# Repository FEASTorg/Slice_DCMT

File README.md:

# DC Motor Driver IC Carrier

DC Motor Driver IC Carrier Slice for BREAD.

## Introduction

[Short introduction on the project.]

## Usage

[Explain how to use the project. Include examples and screenshots if applicable.]

## Documentation

Please refer to the [docs](/docs) for more info.

---

<div align="center">
  
</div>

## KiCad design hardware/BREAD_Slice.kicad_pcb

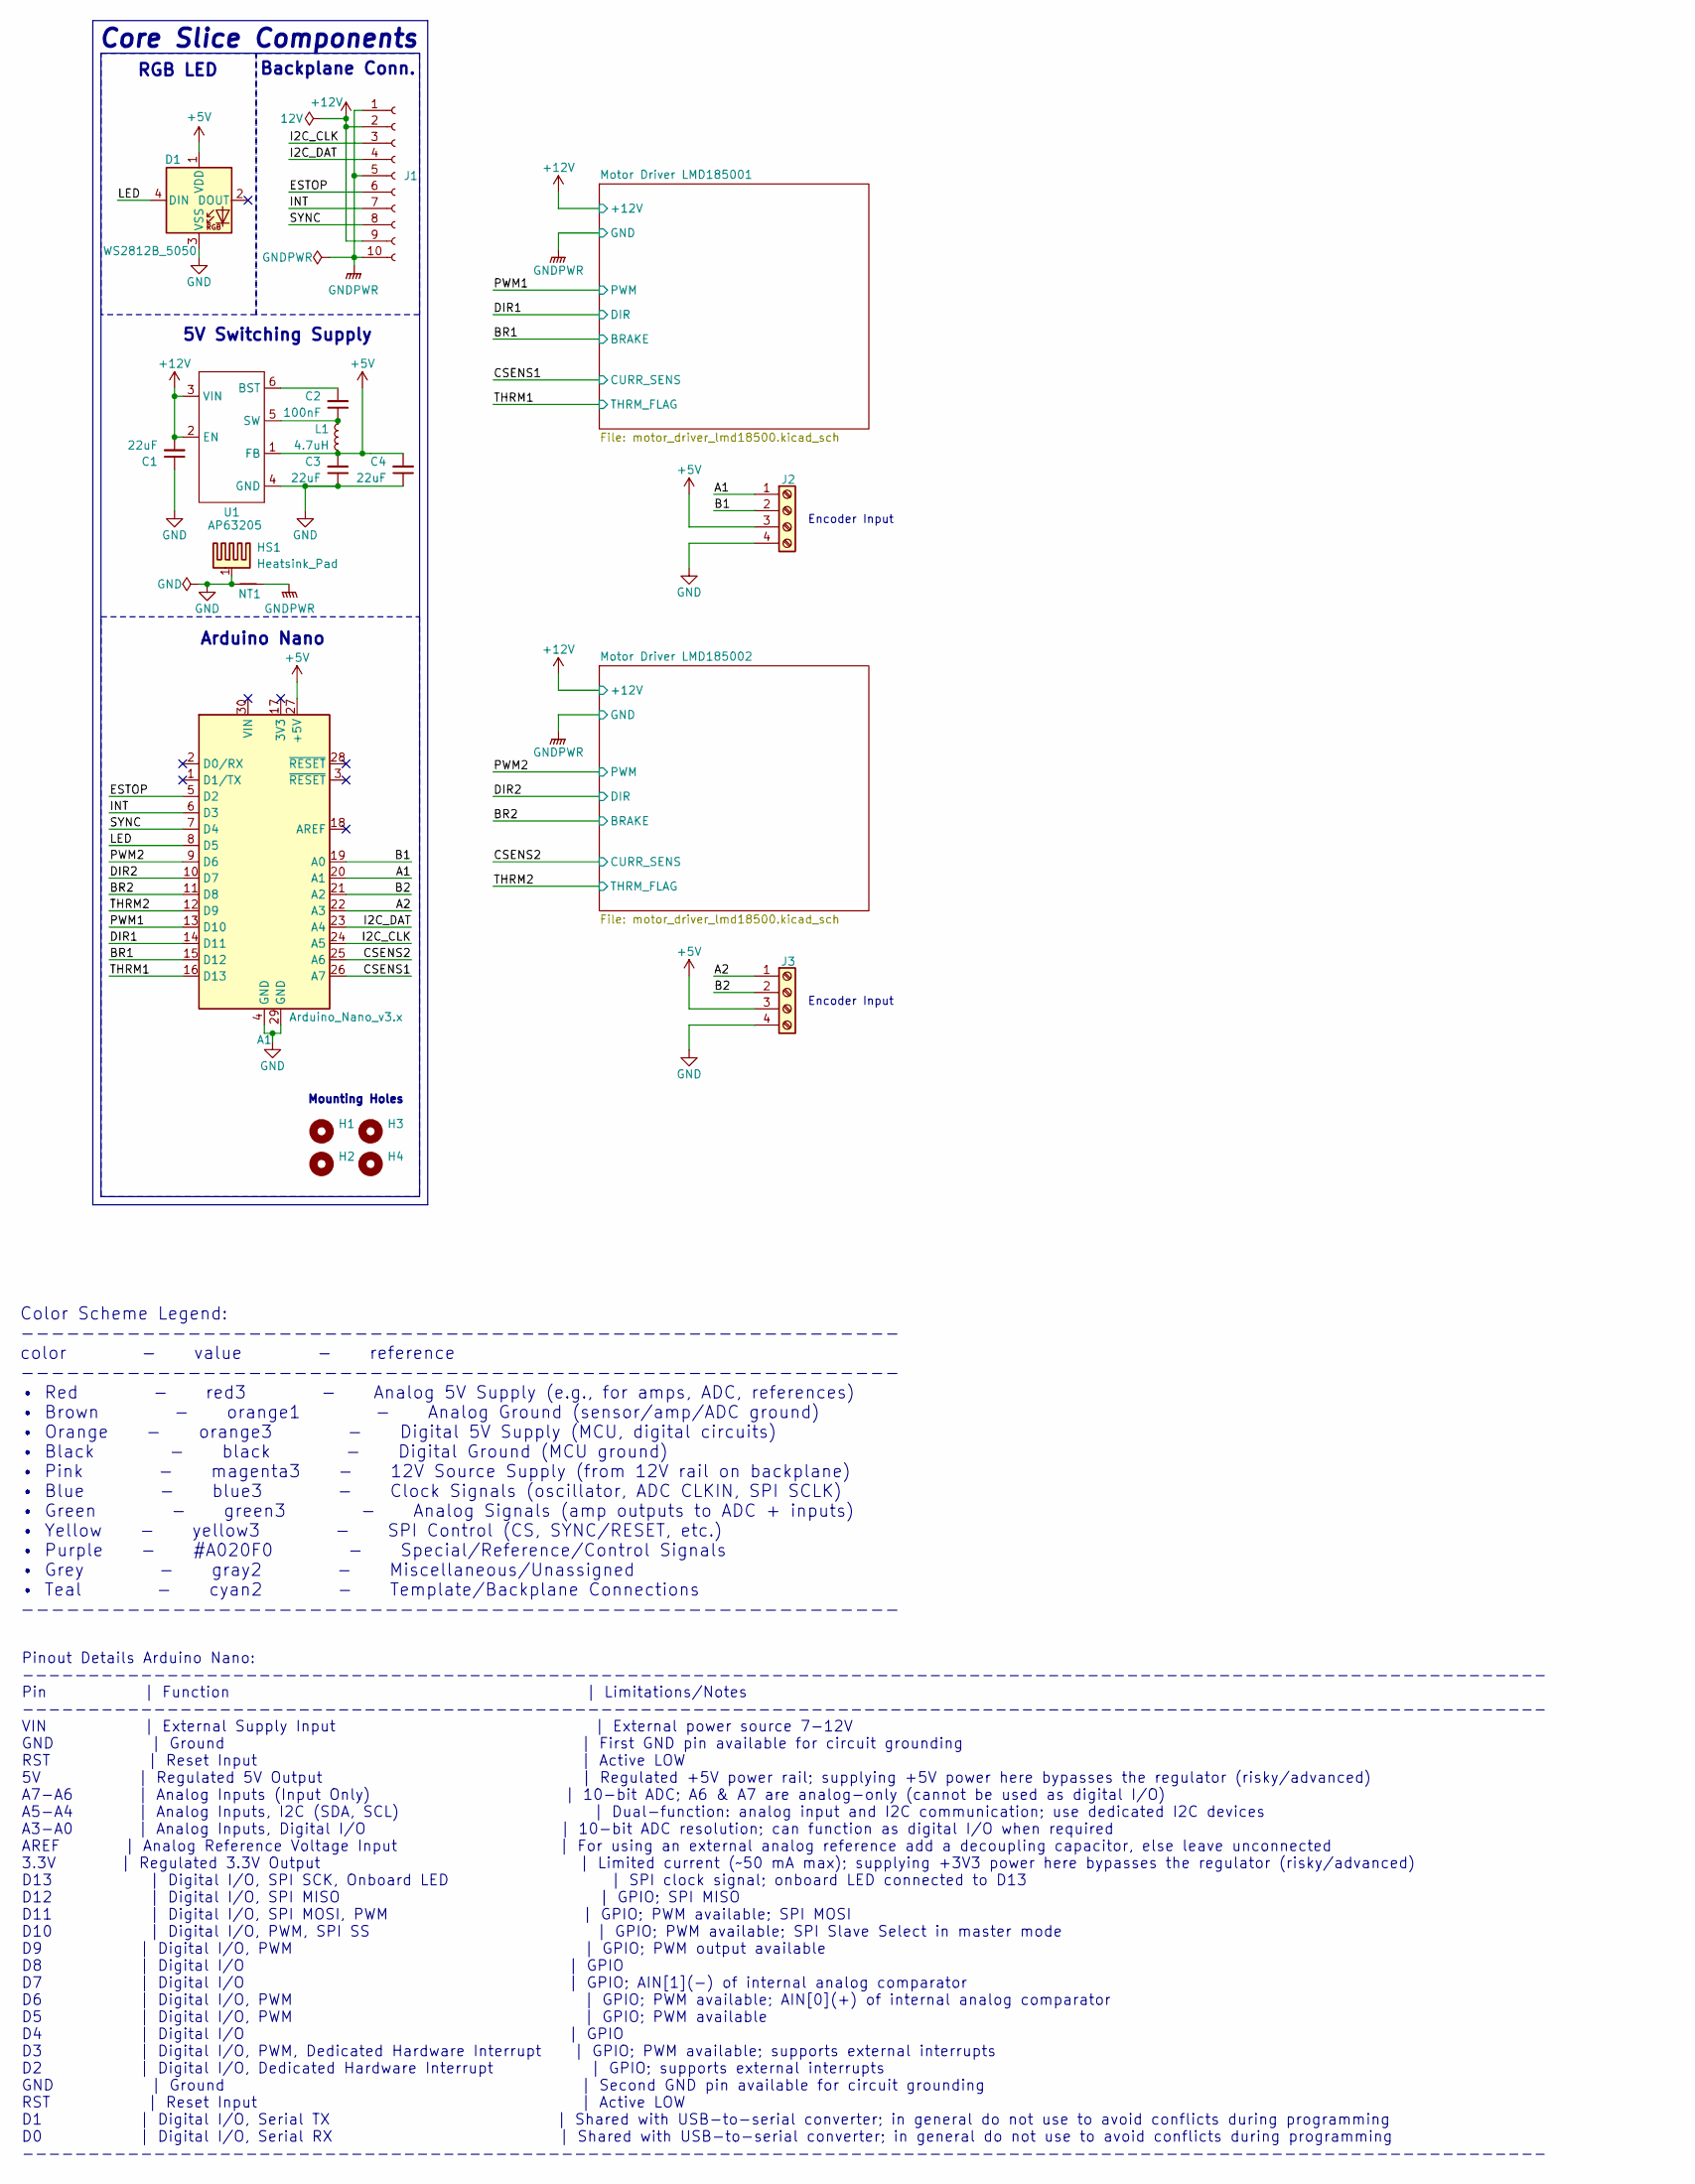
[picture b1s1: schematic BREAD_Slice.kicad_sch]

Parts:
A1: Arduino_Nano_v3.x; Arduino_Nano
C1, C3, C4: 22uF; C_1206_3216Metric
C2: 100nF; C_1206_3216Metric
D1: WS2812B_5050; WS2812-5050-4PIN
H1, H2, H3, H4: MountingHole; MountingHole_5mm
HS1: Heatsink_Pad; Thermal_Pad
J1: Conn_01x10_Socket; PinSocket_1x10_P2.54mm_Horizontal
J2, J3: Screw_Terminal_01x04; TerminalBlock_TE_282834-4_1x04_P2.54mm_Horizontal
L1: 4.7uH; L_1210_3225Metric
NT1: NetTie_2; NetTie-2_SMD_Pad2.0mm
U1: AP63205; SOIC_05WU-7_DIO

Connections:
+5V: A1.27 (+5V), C3.2, C4.2, D1.1 (VDD), J2.3, J3.3, L1.2, U1.1 (FB)
+12V: C1.2, J1.2, J1.9, U1.2 (EN), U1.3 (VIN); also elsewhere on the board
/A1: A1.20 (A1), J2.1
/A2: A1.22 (A3), J3.1
/B1: A1.19 (A0), J2.2
/B2: A1.21 (A2), J3.2
/BR1: A1.15 (D12); also elsewhere on the board
/BR2: A1.11 (D8); also elsewhere on the board
/CSENS1: A1.26 (A7); also elsewhere on the board
/CSENS2: A1.25 (A6); also elsewhere on the board
/DIR1: A1.14 (D11); also elsewhere on the board
/DIR2: A1.10 (D7); also elsewhere on the board
/ESTOP: A1.5 (D2), J1.6
/I2C_CLK: A1.24 (A5), J1.3
/I2C_DAT: A1.23 (A4), J1.4
/INT: A1.6 (D3), J1.7
/LED: A1.8 (D5), D1.4 (DIN)
/PWM1: A1.13 (D10); also elsewhere on the board
/PWM2: A1.9 (D6); also elsewhere on the board
/SYNC: A1.7 (D4), J1.8
/THRM1: A1.16 (D13); also elsewhere on the board
/THRM2: A1.12 (D9); also elsewhere on the board
GND: A1.4 (GND), A1.29 (GND), C1.1, C3.1, C4.1, D1.3 (VSS), HS1.1, J2.4, J3.4, NT1.1, U1.4 (GND)
GNDPWR: J1.1, J1.5, J1.10, NT1.2; also elsewhere on the board
unnamed: C2.2, U1.6 (BST)
unnamed: C2.1, L1.1, U1.5 (SW)

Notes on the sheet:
5V Switching Supply
Pinout Details Arduino Nano: -------------------------------------------------------------------------------------------------------------------- Pin | Function | Limitations/Notes -------------------------------------------------------------------------------------------------------------------- V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
RGB LED
Encoder Input
Color Scheme Legend: ---------------------------------------------------------- color - value - reference ---------------------------------------------------------- • Red - red3 - Analog 5V Supply (e.g., for amps, ADC, references) • Brown - orange1 - Analog Ground (sensor/amp/ADC ground) • Orange -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
Core Slice Components
Arduino Nano
Mounting Holes
Backplane Conn.

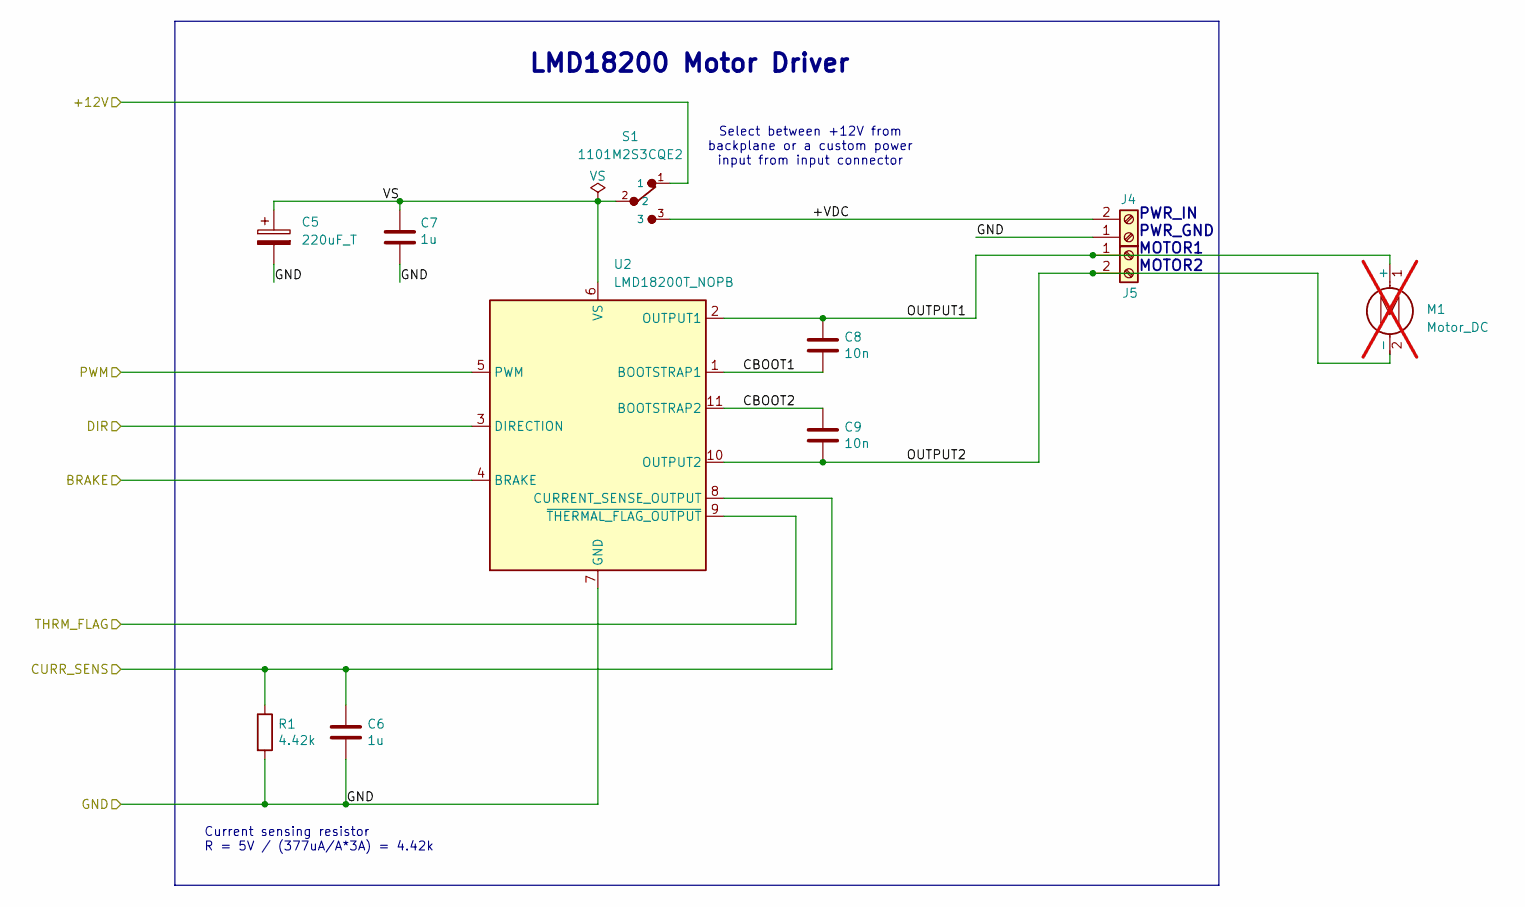
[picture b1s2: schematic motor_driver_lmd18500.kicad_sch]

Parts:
C5: 220uF_T; CP_Radial_D10.0mm_P5.00mm
C6, C7: 1u; C_1206_3216Metric_Pad1.33x1.80mm_HandSolder
C8, C9: 10n; C_0603_1608Metric_Pad1.08x0.95mm_HandSolder
J4, J5: Screw_Terminal_01x02; TerminalBlock_4Ucon_1x02_P3.50mm_Horizontal
M1: Motor_DC; not fitted
R1: 4.42k; R_1206_3216Metric_Pad1.30x1.75mm_HandSolder
S1: 1101M2S3CQE2; SW_Slide-CK-1101M2S3CQE2
U2: LMD18200T_NOPB; TO-220-11_P3.4x5.08mm_StaggerOdd_Lead8.45mm_TabDown

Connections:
+12V: S1.1; also elsewhere on the board
/BR1: U2.4 (BRAKE); also elsewhere on the board
/CSENS1: C6.1, R1.1, U2.8 (CURRENT_SENSE_OUTPUT); also elsewhere on the board
/DIR1: U2.3 (DIRECTION); also elsewhere on the board
/Motor Driver LMD185001/+VDC: J4.2, S1.3
/Motor Driver LMD185001/CBOOT1: C8.2, U2.1 (BOOTSTRAP1)
/Motor Driver LMD185001/CBOOT2: C9.1, U2.11 (BOOTSTRAP2)
/Motor Driver LMD185001/OUTPUT1: C8.1, J5.1, U2.2 (OUTPUT1)
/Motor Driver LMD185001/OUTPUT2: C9.2, J5.2, U2.10 (OUTPUT2)
/Motor Driver LMD185001/VS: C5.1, C7.1, S1.2, U2.6 (VS)
/PWM1: U2.5 (PWM); also elsewhere on the board
/THRM1: U2.9 (~THERMAL_FLAG_OUTPUT); also elsewhere on the board
GNDPWR: C5.2, C6.2, C7.2, J4.1, R1.2, U2.7 (GND); also elsewhere on the board

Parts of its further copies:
C10: 220uF_T; CP_Radial_D10.0mm_P5.00mm
C11, C12: 1u; C_1206_3216Metric_Pad1.33x1.80mm_HandSolder
C13, C14: 10n; C_0603_1608Metric_Pad1.08x0.95mm_HandSolder
J6, J7: Screw_Terminal_01x02; TerminalBlock_4Ucon_1x02_P3.50mm_Horizontal
R2: 4.42k; R_1206_3216Metric_Pad1.30x1.75mm_HandSolder
S2: 1101M2S3CQE2; SW_Slide-CK-1101M2S3CQE2
U3: LMD18200T_NOPB; TO-220-11_P3.4x5.08mm_StaggerOdd_Lead8.45mm_TabDown

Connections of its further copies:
+12V: S2.1; also elsewhere on the board
/BR2: U3.4 (BRAKE); also elsewhere on the board
/CSENS2: C11.1, R2.1, U3.8 (CURRENT_SENSE_OUTPUT); also elsewhere on the board
/DIR2: U3.3 (DIRECTION); also elsewhere on the board
/Motor Driver LMD185002/+VDC: J6.2, S2.3
/Motor Driver LMD185002/CBOOT1: C13.2, U3.1 (BOOTSTRAP1)
/Motor Driver LMD185002/CBOOT2: C14.1, U3.11 (BOOTSTRAP2)
/Motor Driver LMD185002/OUTPUT1: C13.1, J7.1, U3.2 (OUTPUT1)
/Motor Driver LMD185002/OUTPUT2: C14.2, J7.2, U3.10 (OUTPUT2)
/Motor Driver LMD185002/VS: C10.1, C12.1, S2.2, U3.6 (VS)
/PWM2: U3.5 (PWM); also elsewhere on the board
/THRM2: U3.9 (~THERMAL_FLAG_OUTPUT); also elsewhere on the board
GNDPWR: C10.2, C11.2, C12.2, J6.1, R2.2, U3.7 (GND); also elsewhere on the board

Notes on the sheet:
Select between +12V from backplane or a custom power input from input connector
Current sensing resistor R = 5V / (377uA/A*3A) = 4.42k
PWR_IN PWR_GND MOTOR1 MOTOR2
LMD18200 Motor Driver

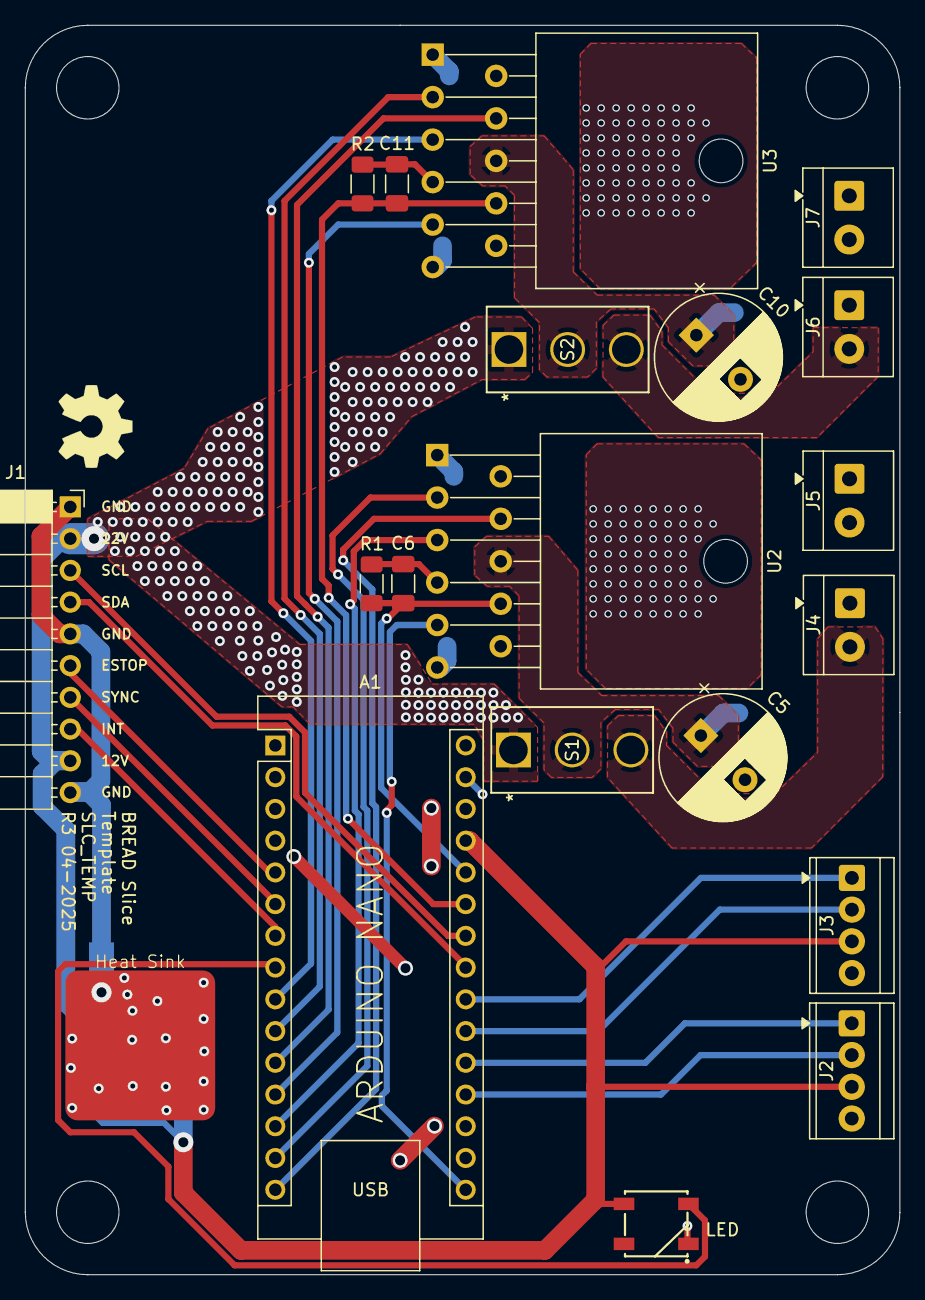
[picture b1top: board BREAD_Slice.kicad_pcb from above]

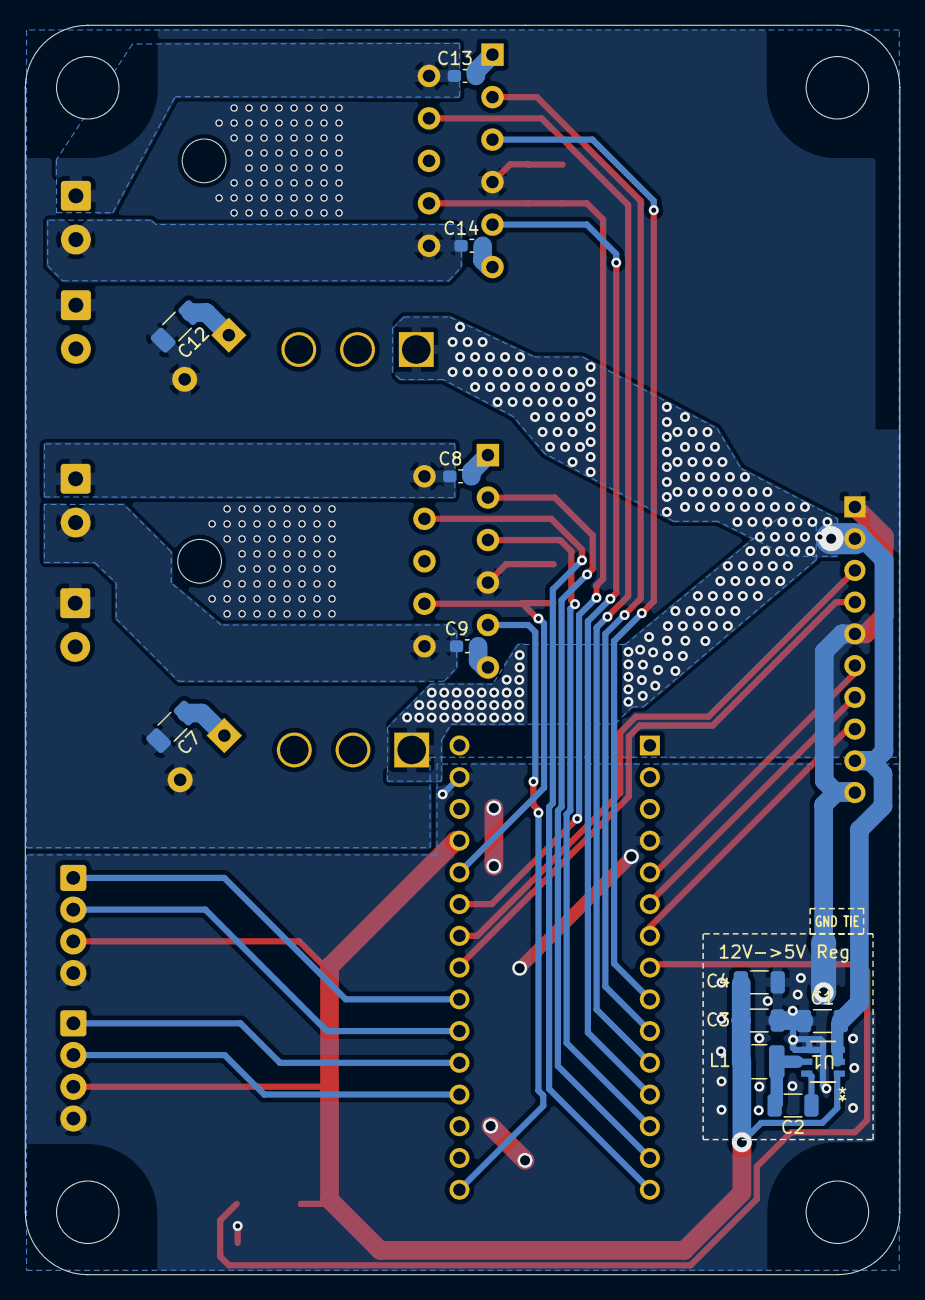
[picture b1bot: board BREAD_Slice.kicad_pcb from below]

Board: 2 copper layers, 70.0 x 100.0 mm, 38 parts (13 on the bottom side), 38 nets.

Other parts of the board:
Logo1: Logo_Open_Hardware_Small; OSHW-Symbol_6.7x6mm_SilkScreen

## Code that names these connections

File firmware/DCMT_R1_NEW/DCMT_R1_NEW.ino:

#include <Wire.h>
// #include <SPI.h>

#define I2C_ADR 14 // Set this however you want

#define DIR1 6
#define MC1 7
#define BR1 8
// #define THRM1 9
#define DIR2 10
#define MC2 11
#define BR2 12
// #define THRM2 13

// #define B2 A0
// #define A2 A1
// #define B1 A2
// #define A1 A3

bool dir1 = 1; // start with forward
bool dir2 = 1;
bool br1 = 1; // start with brake on
bool br2 = 1;

int pwm1, pwm2 = 0; // start with 0 speed

typedef union // Define a float that can be broken up and sent via I2C
{
    float number;
    uint8_t bytes[4];
} FLOATUNION_t;

FLOATUNION_t RX;

byte commandSelect[3];
int8_t speedSelect;
int8_t motor1Speed;
int8_t motor2Speed;
byte motorSelect;
bool changeParam = false;

#define SERIAL_UPDATE_TIME_MS 1000

long lastSerialPrint = 0;

enum Mode
{
    CONTROL,
    WRITE
};

Mode currentMode = CONTROL;

void setup()
{
    pinMode(MC1, OUTPUT);
    pinMode(MC2, OUTPUT);
    pinMode(DIR1, OUTPUT);
    pinMode(DIR2, OUTPUT);
    pinMode(BR1, OUTPUT);
    pinMode(BR2, OUTPUT);

    Serial.begin(115200); // updated baud rate
    Wire.begin(I2C_ADR);
    Wire.onReceive(receiveEvent);
    Wire.onRequest(requestEvent);
}

void loop()
{
    serialCommandHandler();

    if (changeParam)
    {
        switch (motorSelect)
        {
        case 1: // Motor 1 edit
            if (speedSelect == 0)
            {
                br1 = 1;
                pwm1 = 0;
                Serial.println("Motor 1 brake");
            }
            else if (speedSelect < 0 && speedSelect >= -100)
            {
                br1 = 0;
                dir1 = 0;
                speedSelect *= -1;
                pwm1 = map(speedSelect, 0, 100, 0, 255);
                Serial.print("Motor 1 back ");
                Serial.println(pwm1);
            }
            else if (speedSelect > 0 && speedSelect <= 100)
            {
                br1 = 0;
                dir1 = 1;
                pwm1 = map(speedSelect, 0, 100, 0, 255);
                Serial.print("Motor 1 forward ");
                Serial.println(pwm1);
            }
            else
            {
                Serial.println("Invalid Entry, nothing will be changed");
            }
            break;

        case 2: // motor 2 edit
            if (speedSelect == 0)
            {
                br2 = 1;
                pwm2 = 0;
                Serial.println("Motor 2 brake");
            }
            else if (speedSelect < 0 && speedSelect >= -100)
            {
                br2 = 0;
                dir2 = 0;
                speedSelect *= -1;
                pwm2 = map(speedSelect, 0, 100, 0, 255);
                Serial.print("Motor 2 back ");
                Serial.println(pwm2);
            }
            else if (speedSelect > 0 && speedSelect <= 100)
            {
                br2 = 0;
                dir2 = 1;
                pwm2 = map(speedSelect, 0, 100, 0, 255);
                Serial.print("Motor 2 forward ");
                Serial.println(pwm2);
            }
            else
            {
                Serial.println("Invalid Entry, nothing will be changed");
            }
            break;

        default:
            Serial.println("oopsie poopsie, that's not a command, silly");
            break;
        }
        changeParam = false;
    }

    digitalWrite(DIR1, dir1);
    analogWrite(MC1, pwm1);
    digitalWrite(BR1, br1);
    digitalWrite(DIR2, dir2);
    analogWrite(MC2, pwm2);
    digitalWrite(BR2, br2);

    printOutput();
}

void printOutput()
{
    if (millis() - lastSerialPrint >= SERIAL_UPDATE_TIME_MS)
    {
        Serial.print("SpeedSelect: ");
        Serial.print(speedSelect);
        Serial.print(", MotorSelect: ");
        Serial.print(motorSelect);
        Serial.print(" || ");
        Serial.print("Speed1: ");
        Serial.print(motor1Speed);
        Serial.print(", PWM1: ");
        Serial.print(pwm1);
        Serial.print(", Dir1: ");
        Serial.print(dir1);
        Serial.print(", Brake1: ");
        Serial.print(br1);
        Serial.print(", Speed2: ");
        Serial.print(motor2Speed);
        Serial.print(", PWM2: ");
        Serial.print(pwm2);
        Serial.print(", Dir2: ");
        Serial.print(dir2);
        Serial.print(", Brake2: ");
        Serial.println(br2);

        lastSerialPrint = millis();
    }
}

void serialCommandHandler()
{
    if (Serial.available())
    {
        String command = Serial.readStringUntil('\n');
        command.trim();
        char cmdType = command.charAt(0);

        if (cmdType == 'M')
        { // Mode switch command: "M,0" for CONTROL, "M,1" for WRITE
            int mode = command.substring(2).toInt();
            if (mode == 0)
            {
                currentMode = CONTROL;
                Serial.println("Switched to CONTROL mode");
            }
            else if (mode == 1)
            {
                currentMode = WRITE;
                Serial.println("Switched to WRITE mode");
            }
        }
        else if (cmdType == 'W')
        { // Motor update command in the format: "W,<motorSelect>,<speedSelect>"
            int firstComma = command.indexOf(',');
            int secondComma = command.indexOf(',', firstComma + 1);
            if (firstComma != -1 && secondComma != -1)
            {
                motorSelect = command.substring(firstComma + 1, secondComma).toInt();
                speedSelect = command.substring(secondComma + 1).toInt();
                changeParam = true;
                Serial.print("Serial update: motorSelect = ");
                Serial.print(motorSelect);
                Serial.print(", speedSelect = ");
                Serial.println(speedSelect);
            }
            else
            {
                Serial.println("Invalid command format for motor update.");
            }
        }
        else
        {
            Serial.println("Invalid serial command!");
        }
    }
}

void requestEvent()
{
    Serial.print("Sending: ");
    Serial.print(motor1Speed);
    Serial.print(", ");
    Serial.println(motor2Speed);

    Wire.write(motor1Speed);
    Wire.write(motor2Speed);
}

void receiveEvent(int howMany)
{
    int i = 0;
    while (Wire.available())
    {
        commandSelect[i] = Wire.read();
        Serial.print(i);
        Serial.print("-> ");
        Serial.print(commandSelect[i]);
        Serial.print(", ");
        i++;
    }
    Serial.println();
    motorSelect = commandSelect[0];
    speedSelect = commandSelect[1];

    switch (motorSelect)
    {
    case 1:
        motor1Speed = speedSelect;
        break;
    case 2:
        motor2Speed = speedSelect;
        break;
    }

    changeParam = true;
}

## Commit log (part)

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2025-09-06 📄 Auto-generate KiBot index page
2025-09-07 docs: add architecture, changelog, and testing templates; fix TODO formatting; rename orchestrate-docs workflow
2025-09-07 Add BOM_DCMT_R1.ods to hardware archive; update .indexignore to remove as its outside docs/ now
2025-09-07 🔁 Auto-generate docs index
2025-09-07 chore: rename scripts to be consistent
2025-09-07 docs: add front matter and switch to just-the-docs theme
2025-09-07 docs: add README.md to ignore lists and update front matter to exclude main index from nav
2025-09-07 docs (ci): generate images to assets folder to view on page
2025-09-07 📄 KiBot index + board renders (auto)
2025-09-07 remove readme from index ignore
2025-09-07 add assets to indexignore, add closing quote in index_template front matter, and update makefile to include image targets
2025-09-07 makefile: remove unneeded escape key
2025-09-07 makefile: fix pcb_fab target by removing invalid print_pcb step
2025-09-07 fix: use space-separated KiBot stages in Makefile to avoid preflight errors
2025-09-07 makefile plz work
2025-09-07 makefile plz plz work
2025-09-07 fix(kibot): use lowercase 'png' for pcbdraw format to avoid config error
2025-09-07 fix(pcbdraw): render true bottom view by removing mirror from back image
2025-09-07 fix(pcbdraw): render true bottom view by using correct flags
2025-09-07 enhance: remove yq downloads
2025-09-07 fix(ci): changed syntax to use shipped version of yq (go)
2025-09-07 restore yq installs
2025-09-07 better layout images
2025-09-07 ci: remove yq dependency from workflows using native Python parsing
2025-09-07 add GitHub Actions cache for KiBot 3D model downloads to speed up Fab job
2025-09-07 chore: push ci
2025-09-07 ci(kibot): add persistent 3D model cache with restore fallback and retries
2025-09-07 change pic presentation to trigger ci
2025-09-07 add assets/ dir to exclude from publishing
2025-09-07 add interactive html bom
2025-09-07 resolve glob patterns in KiBot index generator to expand artifact wildcards
2025-09-07 change script
2025-09-07 restore script
2025-09-07 fix: remove assets from exclude so images render, old page was vestigal
2025-09-07 hopefuilly fix da glob
2025-09-07 ci(fix): resolve globs + add project name
2025-09-07 ci(fix): case-insensitive match + ibom path update for artifact resolution
2025-09-07 try fix blrh
2025-09-07 add debug to kibot index workflow
2025-09-07 fix: artifact name pattern for ibom html
2025-09-07 fix: deploy all matching KiBot artifacts (avoid missing iBoM.html)
2025-09-07 clean up KiBot deploy/index workflows: safer shell, remove debug, unify style
2025-09-07 chore: clean and finalize KiBot and index scripts for Jekyll
2025-09-07 chore(ci): remove docs index generator workflow
2025-09-07 workflows: orchestrate-docs rename to docs-pipeline, generate-kibot-index rename to publish-kibot
2025-09-07 ci: use centralized slice-infra workflows for KiBot + Pages
2025-09-07 chore(ci): trigger workflow with new infra
2025-09-07 refactor docs: remove .indexignore, clear TODO.md, and update descriptions.
2025-09-14 rename: slice-infra --> bread-infra
2025-09-14 docs(config): aux links and color scheme (remote)
2025-09-17 revise breaking and type id
2025-09-25 minor: rename _ to - in componenets sourcing docc
2025-10-15 update firmwares for diff brds
2025-10-15 add version number
2025-10-15 add changelogs to coordinate with versions
2025-10-15 update last addresss uploaded
2025-10-15 rename apprpriate to reflect hw revisions
2025-10-16 move version tag
2025-10-16 minor: add comment striong on version to remind to update
2025-10-22 rename and move firmware to split arduino and pio
2026-01-22 add old old gen0 scripts
2026-01-22 organize fw properly
2026-01-22 trigger fresh rerun
2026-01-22 trigger rerun
2026-02-01 review and revise for current template and kmlib
2026-03-09 clean up repo
2026-03-09 split fw
2026-03-09 update gitignore
2026-03-09 feat: initial conversion to new crumbs
2026-03-10 firmware: implement the gen1 / gen2 env split
2026-03-10 feat: add nano every support and note dcmotorservo as todo
2026-03-10 chore: archive old fw
2026-03-10 hardening: add checks for dev context and version checks
2026-03-10 feat: add local shared header in prep for shared contract repo
2026-03-14 feat: use published contracts
2026-03-14 add bitwise caps reply for closed vs open loop hw
2026-03-14 clean out legacy code after new contract cutover
2026-03-14 add i2c address selection from ini
2026-03-15 refactor(dcmt): separate hw gen from control capability and mcu speed profile
2026-03-15 chore(dcmt): cut over to published LMD18200 package and remove vendored lib
2026-03-15 add base env for nano vs nano every
2026-03-15 feat: restore the proper dcmotorservo closed loop functionality
2026-03-18 feat: make crumbs debug flag via build config
2026-03-18 clean up string handling
2026-03-18 add global decs. for PIDTunings
2026-03-18 remove setpoint gating
2026-03-18 add comment clarifying that moveTo is idempotent
2026-03-19 debounce estop and change to input pullup
2026-03-19 mitigate reapplication of PID settings
2026-03-19 feat(crumbs): payload reply is fixed and invalid data has explicit sentinels for invalid data during closed loop caps. config
2026-03-19 add back version, idk how that happened
2026-03-19 fix: function declaration ordering for servo1/2
2026-03-19 add gitattributes to normalzie across platforms
2026-03-19 pollEStop() now uses a static CRGB lastLed = CRGB::Black local to gate FastLED.show() to transitions only
2026-03-19 remove duplicate (drift prone) version in favour of the canonical version defined in contract
2026-03-19 inset encoder range by 1 to avoid falsely reporting sentinel value
2026-04-02 chore: bump contracts (0.4.1) and crumbs (0.12.0) versions
2026-04-02 chore: clean
2026-04-20 refactor: org casing rename from 'FEASTorg' to 'feastorg'
2026-05-12 feat(fw): add watchdog timer with 1s timeout
2026-05-12 fix(fw): protect shared state with interrupt guards
    Use snapshot-in/commit-out pattern in motorControlLogic to prevent
    torn reads between I2C ISR (reply_get_state) and main loop writes.
    Add noInterrupts/interrupts guards around processEStop writes.
2026-05-12 fix(fw): replace String with static buffer in serial commands
    Eliminates all heap allocations from the serial command parser.
    Uses a 64-byte static char buffer and C string functions (atol,
    strtod, strcmp_P) to prevent heap fragmentation on long-running
    ATmega328 devices.
2026-05-12 fix(fw): portability fixes for megaAVR targets
    Simplify WDT include guard, fix Timing.lastSerialPrint to unsigned
    long to match millis() return type and prevent signed overflow.
2026-05-12 fix(fw): guard empty string in serial command trim
2026-05-17 add retrospective changelog
2026-05-17 fix: race commit with local motor pwm
2026-05-20 Add slice.yaml manifest (schema v1.0 pilot)
2026-05-20 Add CI workflow with manifest validation
2026-06-11 chore: update crumbs contract dependencies
2026-06-11 ci: retrigger after schema-v1.0 tag creation
2026-06-11 chore: update crumbs contract dependencies (#1)
    * chore: update crumbs contract dependencies
    * ci: retrigger after schema-v1.0 tag creation
